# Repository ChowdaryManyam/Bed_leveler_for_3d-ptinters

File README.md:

# Bed_leveler_for_3d-ptinters

A very simple and easily modifiable and adaptable PCB for leveling the beds of 3d-printers and CNC machines. 
It does come with a hole and can be used as a keychain, for ease of carrying it arround in style.
A single layer PCB with no/low drills(Only 2 drills for the THT-led, Even those can be used as-is by placing an SMT-LED).

https://github.com/ChowdaryManyam/Bed_leveler_for_3d-ptinters/assets/67430518/a5fa3f9a-c688-4bbf-8ffc-a4bfc6a4cefe

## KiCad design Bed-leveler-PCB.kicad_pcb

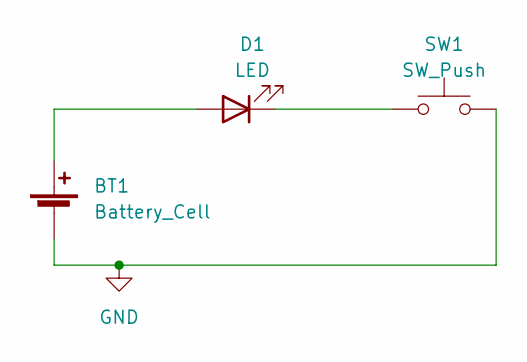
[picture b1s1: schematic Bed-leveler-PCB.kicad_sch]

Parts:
BT1: Battery_Cell; BatteryHolder_Keystone_1060_1x2032
D1: LED; LED_D2.0mm_W4.8mm_H2.5mm_FlatTop
SW1: SW_Push; SW_SPST_Omron_B3FS-100xP

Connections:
unnamed: BT1.1 (+), D1.2 (A)
unnamed: BT1.2 (-), SW1.2
unnamed: D1.1 (K), SW1.1

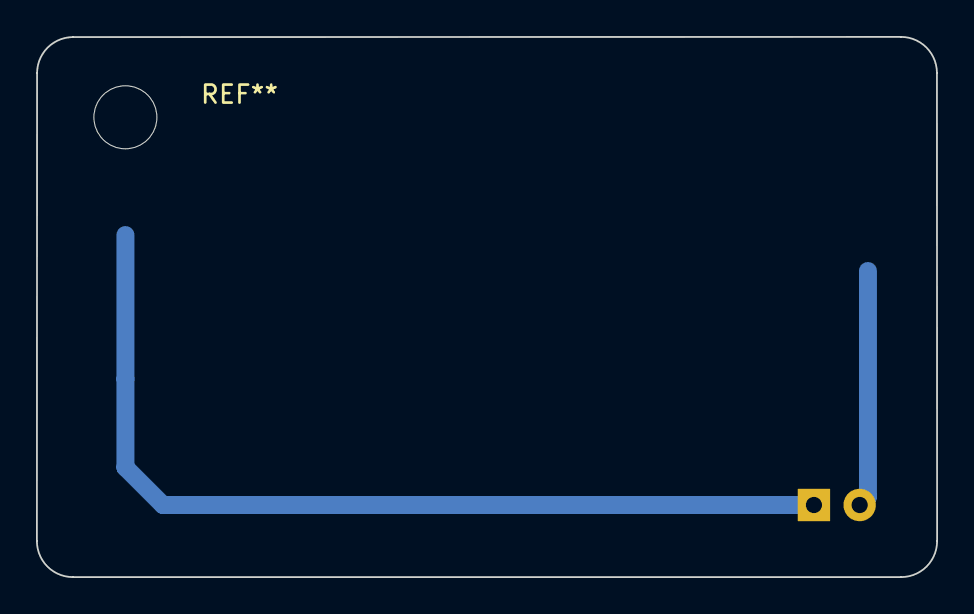
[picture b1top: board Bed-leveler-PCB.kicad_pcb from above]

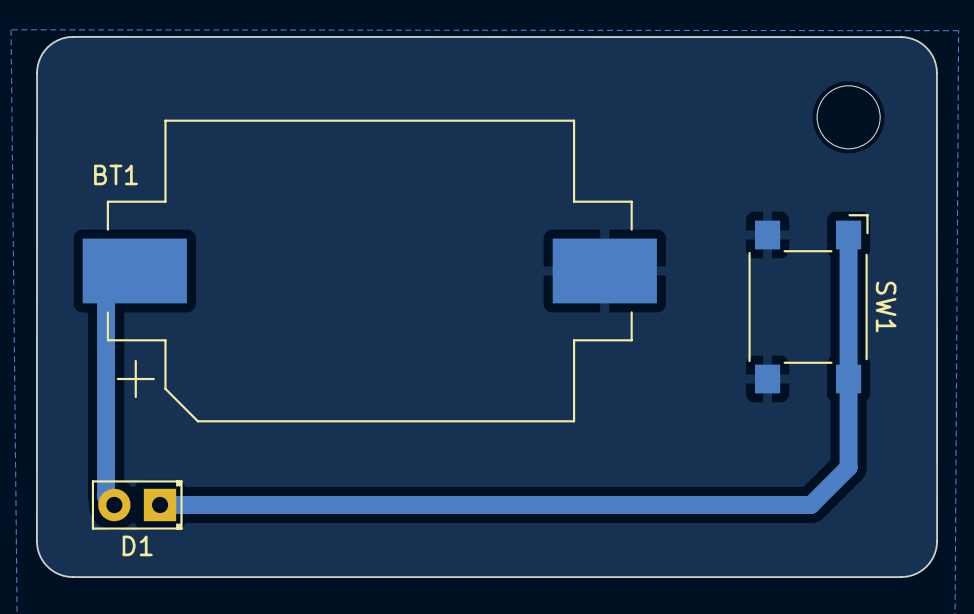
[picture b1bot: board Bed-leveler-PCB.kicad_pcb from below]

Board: 2 copper layers, 50.0 x 30.0 mm, 3 parts (3 on the bottom side), 3 nets.
